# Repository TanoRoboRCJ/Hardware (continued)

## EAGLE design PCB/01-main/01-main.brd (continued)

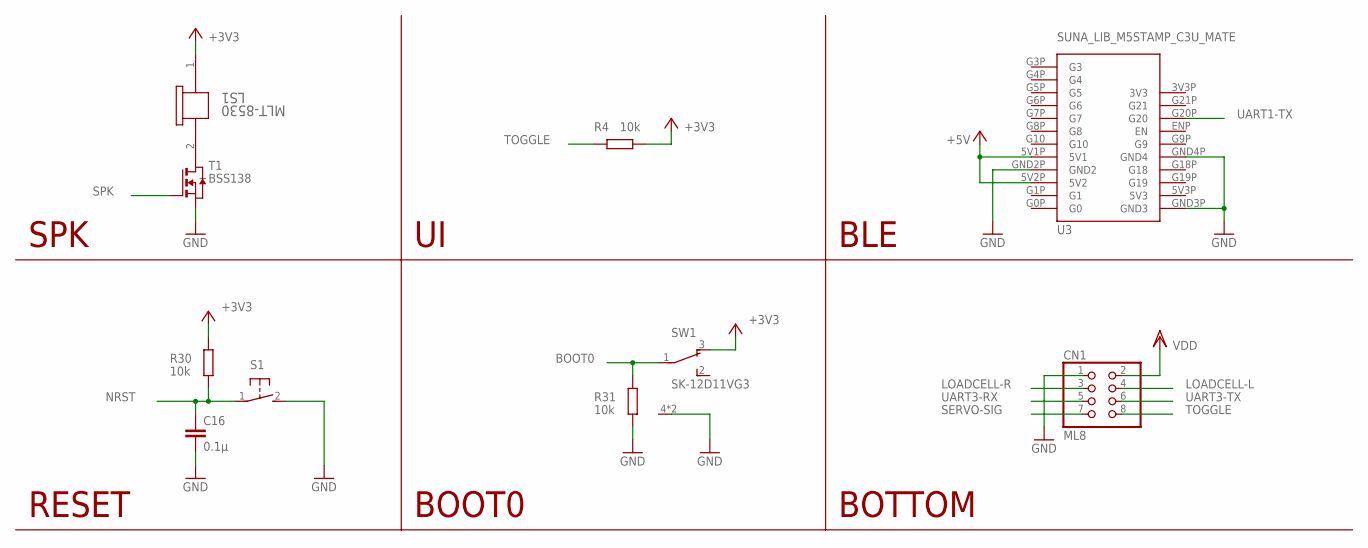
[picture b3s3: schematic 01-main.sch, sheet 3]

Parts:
C16: 0.1µ; C0603
CN1: ML8; ML6L
LS1: MLT-8530; MLT-8530_JHE
R4, R30, R31: 10k; R0402
S1: 31-XX; B3F-31XX
SW1: SK-12D11VG3
T1: BSS138; SOT-23
U3: SUNA_LIB_M5STAMP_C3U_MATE; SUNA_LIB_M5STAMPC3UMATE

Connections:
+3V3: LS1.1, R4.1, R30.1, SW1.3 (O); also elsewhere on the board
+5V: U3.5V1P (5V1), U3.5V2P (5V2); also elsewhere on the board
BOOT0: R31.1, SW1.1; also elsewhere on the board
GND: C16.2, CN1.1, R31.2, S1.2 (S), SW1.4 (CASE), SW1.5 (CASE), T1.2 (S), U3.GND2P (GND2), U3.GND3P (GND3), U3.GND4P (GND4); also elsewhere on the board
LOADCELL-L: CN1.4; also elsewhere on the board
LOADCELL-R: CN1.3; also elsewhere on the board
unnamed: LS1.2, T1.1 (D)
NRST: C16.1, R30.2, S1.1; also elsewhere on the board
SERVO-SIG: CN1.7; also elsewhere on the board
SPK: T1.3 (G); also elsewhere on the board
TOGGLE: CN1.8, R4.2; also elsewhere on the board
UART1-TX: U3.G20P (G20); also elsewhere on the board
UART3-RX: CN1.5; also elsewhere on the board
UART3-TX: CN1.6; also elsewhere on the board
VDD: CN1.2; also elsewhere on the board

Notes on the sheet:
BOTTOM
SPK
RESET
BOOT0
BLE

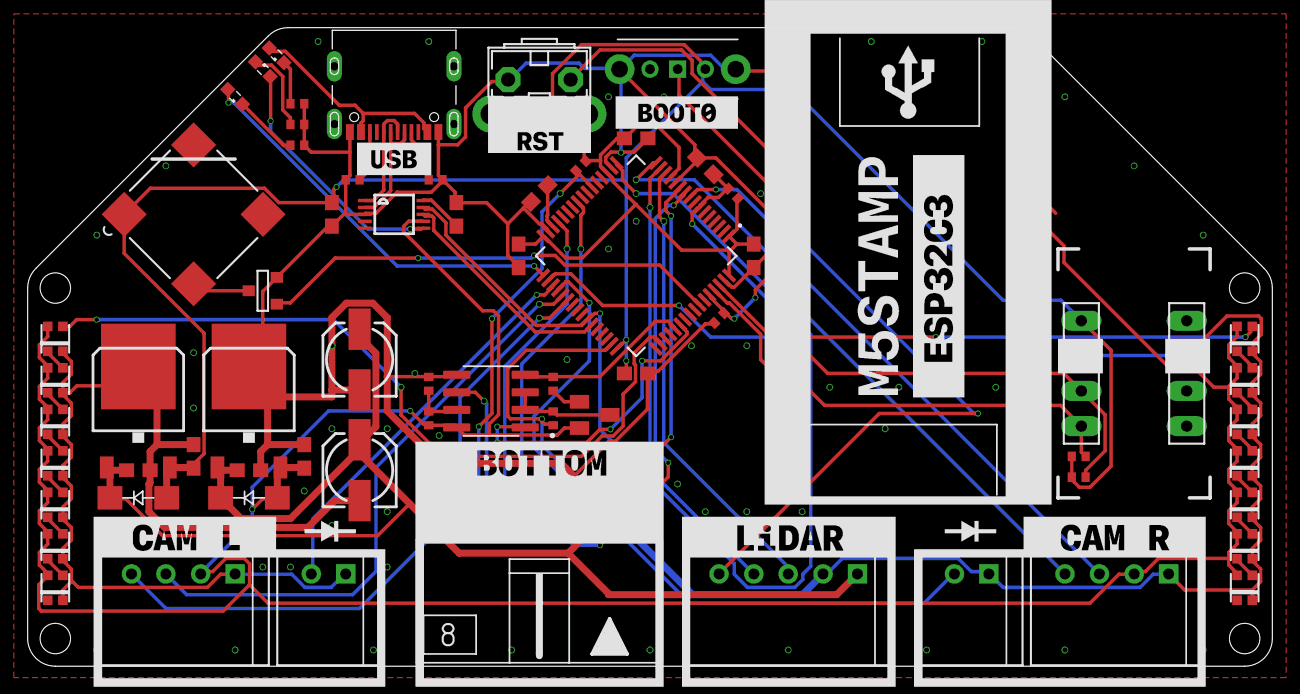
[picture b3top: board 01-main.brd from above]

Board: 2 copper layers, 90.0 x 46.2 mm, 66 parts (0 on the bottom side), 58 nets.

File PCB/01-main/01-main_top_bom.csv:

Comment,Designator,Footprint,LCSC Part #,,,,,,,
0.1µ,C2 C3 C4 C5 C6 C7 C11 C14 C16,C0603,C14663,,,,,,,
1N4001,D1 D2,SMA-DO214AC,C727079,,,,,,,
1µ,C8 C17,C0603,C15849,,,,,,,
2k2,R15 R16,R0402,C25879,,,,,,,
4.7µ,C1,C0603,C19666,,,,,,,
5k1,R1 R2,R0402,C25879,,,,,,,
7.5k,R17,R0402,C25918,,,,,,,
10k,R4 R12 R13 R30 R31,R0402,C25744,,,,,,,
20k,R14,R0402,C25765,,,,,,,
100μ,C9 C13,153CLV-0505,C72487,,,,,,,
270,R3 R10 R32,R0402,C25099,,,,,,,
BLUE,LED15,SML0603,C118339,,,,,,,
BSS138,T1,SOT-23,C112239,,,,,,,
C1015,Q1,SOT23,C181170,,,,,,,
CH340ESMD,U1,MSOP10,C99652,,,,,,,
MAX485ESA+T,U5,SOIC127P600X175-8N,MAX485ED,,,,,,,
MLT-8530,LS1,MLT-8530_JHE,C94599,,,,,,,
REG-3V3,REG1,MYPARTS_D-PAK_TO252AA,,,,,,,,
REG-5V,REG2,MYPARTS_D-PAK_TO252AA,,,,,,,,
STM32F446RET6,U2,LQFP64-10X10MM,C69336,,,,,,,
WHITE,LED17 LED18,SML0603,C389521,,,,,,,
WS2812B_2020,LED1 LED2 LED3 LED4 LED5 LED6 LED7 LED8 LED9 LED10 LED11 LED12 LED13 LED14,WS2812B_2020,C965555,,,,,,,
usb-c,X2,USB_C_CUSB31-CFM2AX-01-X,C2987386,,,,,,,

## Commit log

2024-01-16 ✨ ライセンス
2024-01-16 🎉 INUWASHI基板を移管
2024-01-18 ✏️ メイン基板部品配置完了
2024-01-18 ⚡️基礎配線完了
2024-01-18 ✏️ i2Cのプルアップ抵抗の位置を変更
2024-01-18 ⚡️ ERC
2024-01-18 ⚡️ パスコンの位置を調整
2024-01-18 ✨ メイン配線
2024-01-18 ⚡️ 10milに改良
2024-01-18 ✨ ビアうち完了
2024-01-19 ✨ シルク完了
2024-01-20 ✨ 下段配線（ENC以外）完了
2024-01-21 ✏️ Update README.md
2024-01-22 ✨エンコーダー配線完了
2024-01-23 ✨ 下段完成
2024-01-23 ✨ LIDAR
2024-01-23 ✏️ 一旦保存
2024-01-23 ✨ 基本配線完了
2024-01-23 ✨ とりあえずできた、一晩寝かせる
2024-01-25 ✨ LiDARのシルク入れ完了
2024-01-26 ♻️ 再配線中
2024-01-26 ♻️ ほぼ完成
2024-01-26 ✨ 完了
